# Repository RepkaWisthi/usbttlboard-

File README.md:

# usbttlboard-
usb ttl with ch340 IC

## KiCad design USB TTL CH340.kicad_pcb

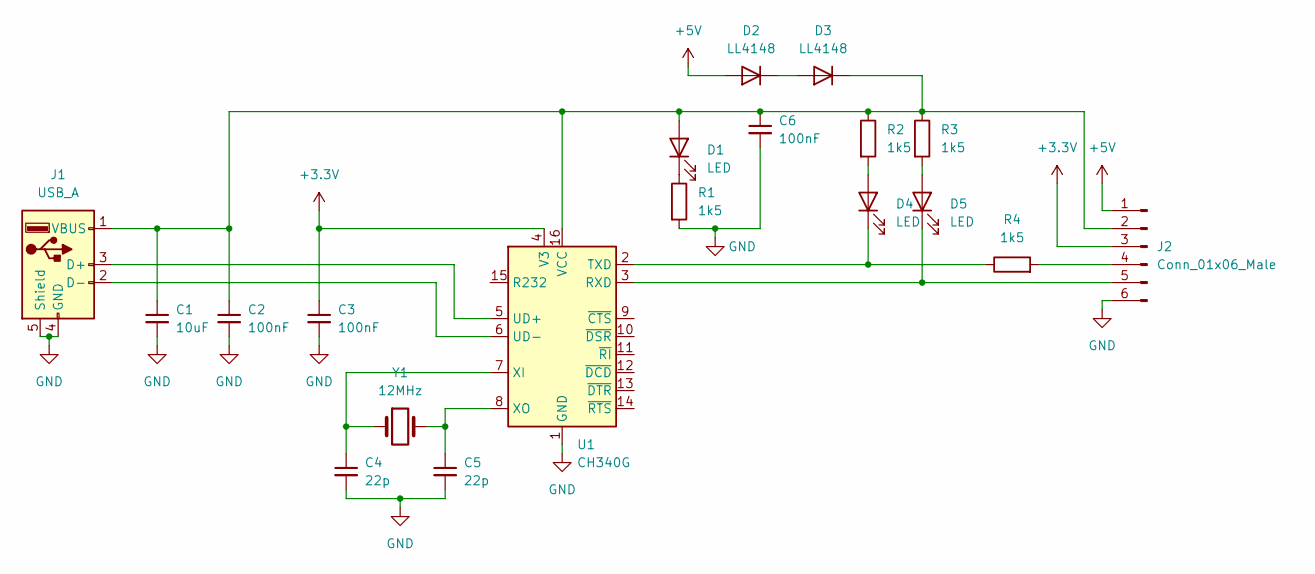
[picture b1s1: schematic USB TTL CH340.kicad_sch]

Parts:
C1: 10uF; C_0603_1608Metric
C2, C3, C6: 100nF; C_0603_1608Metric
C4, C5: 22p; C_0603_1608Metric
D1, D4, D5: LED; LED_0603_1608Metric
D2, D3: LL4148; D_MiniMELF
J1: USB_A; USB_A_CONNFLY_DS1095-WNR0
J2: Conn_01x06_Male; PinHeader_1x06_P2.54mm_Horizontal
R1, R2, R3, R4: 1k5; R_0603_1608Metric
U1: CH340G; SOIC-16_3.9x9.9mm_P1.27mm
Y1: 12MHz; Crystal_HC49-4H_Vertical

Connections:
+3.3V: C3.1, J2.3, U1.4 (V3)
+5V: D2.2 (A), J2.1
GND: C1.2, C2.2, C3.2, C4.2, C5.2, C6.2, J1.4 (GND), J1.5 (Shield), J2.6, R1.2, U1.1 (GND)
unnamed: C1.1, C2.1, C6.1, D1.2 (A), D3.1 (K), J1.1 (VBUS), J2.2, R2.1, R3.1, U1.16 (VCC)
unnamed: C4.1, U1.7 (XI), Y1.1
unnamed: C5.1, U1.8 (XO), Y1.2
unnamed: D1.1 (K), R1.1
unnamed: D2.1 (K), D3.2 (A)
unnamed: D4.1 (K), R4.1, U1.2 (TXD)
unnamed: D4.2 (A), R2.2
unnamed: D5.1 (K), J2.5, U1.3 (RXD)
unnamed: D5.2 (A), R3.2
unnamed: J1.2 (D-), U1.6 (UD-)
unnamed: J1.3 (D+), U1.5 (UD+)
unnamed: J2.4, R4.2

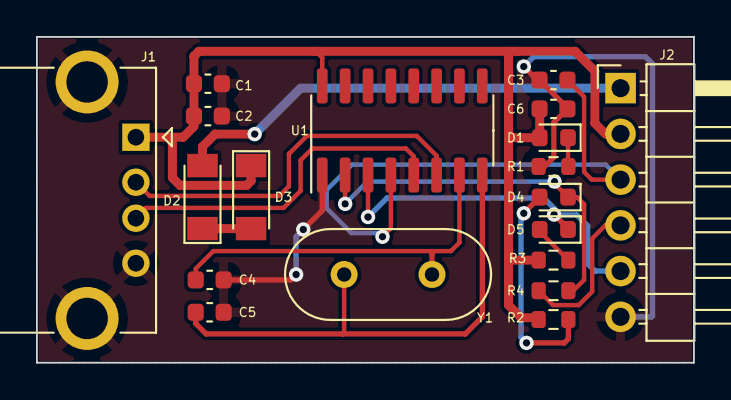
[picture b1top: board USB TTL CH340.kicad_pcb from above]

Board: 2 copper layers, 36.5 x 18.1 mm, 19 parts (0 on the bottom side), 15 nets.
